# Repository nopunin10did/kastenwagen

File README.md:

# Kastenwagen 1840

Kastenwagen 1840 is a 40% keyboard with a mini-numpad and dedicated arrows.  The main alpha block is 13.75u long, allowing for more dedicated punctuation keys (or non-English letters) to be paired with common Minivan-like mod keys.

Kastenwagen 48 is a similar keyboard that replaces the mini-numpad with a small macro column.

For more information, join the [NoPunIn10Key Discord](https://discord.gg/sku2Y6w).

* Keyboard Maintainer: [Alex Ronke](https://nopunin10did.com/), also known as [NoPunIn10Did](https://github.com/NoPunIn10Did)
* Hardware Supported: Kastenwagen 1840 (2021 June)
* Hardware Availability: Currently by request only

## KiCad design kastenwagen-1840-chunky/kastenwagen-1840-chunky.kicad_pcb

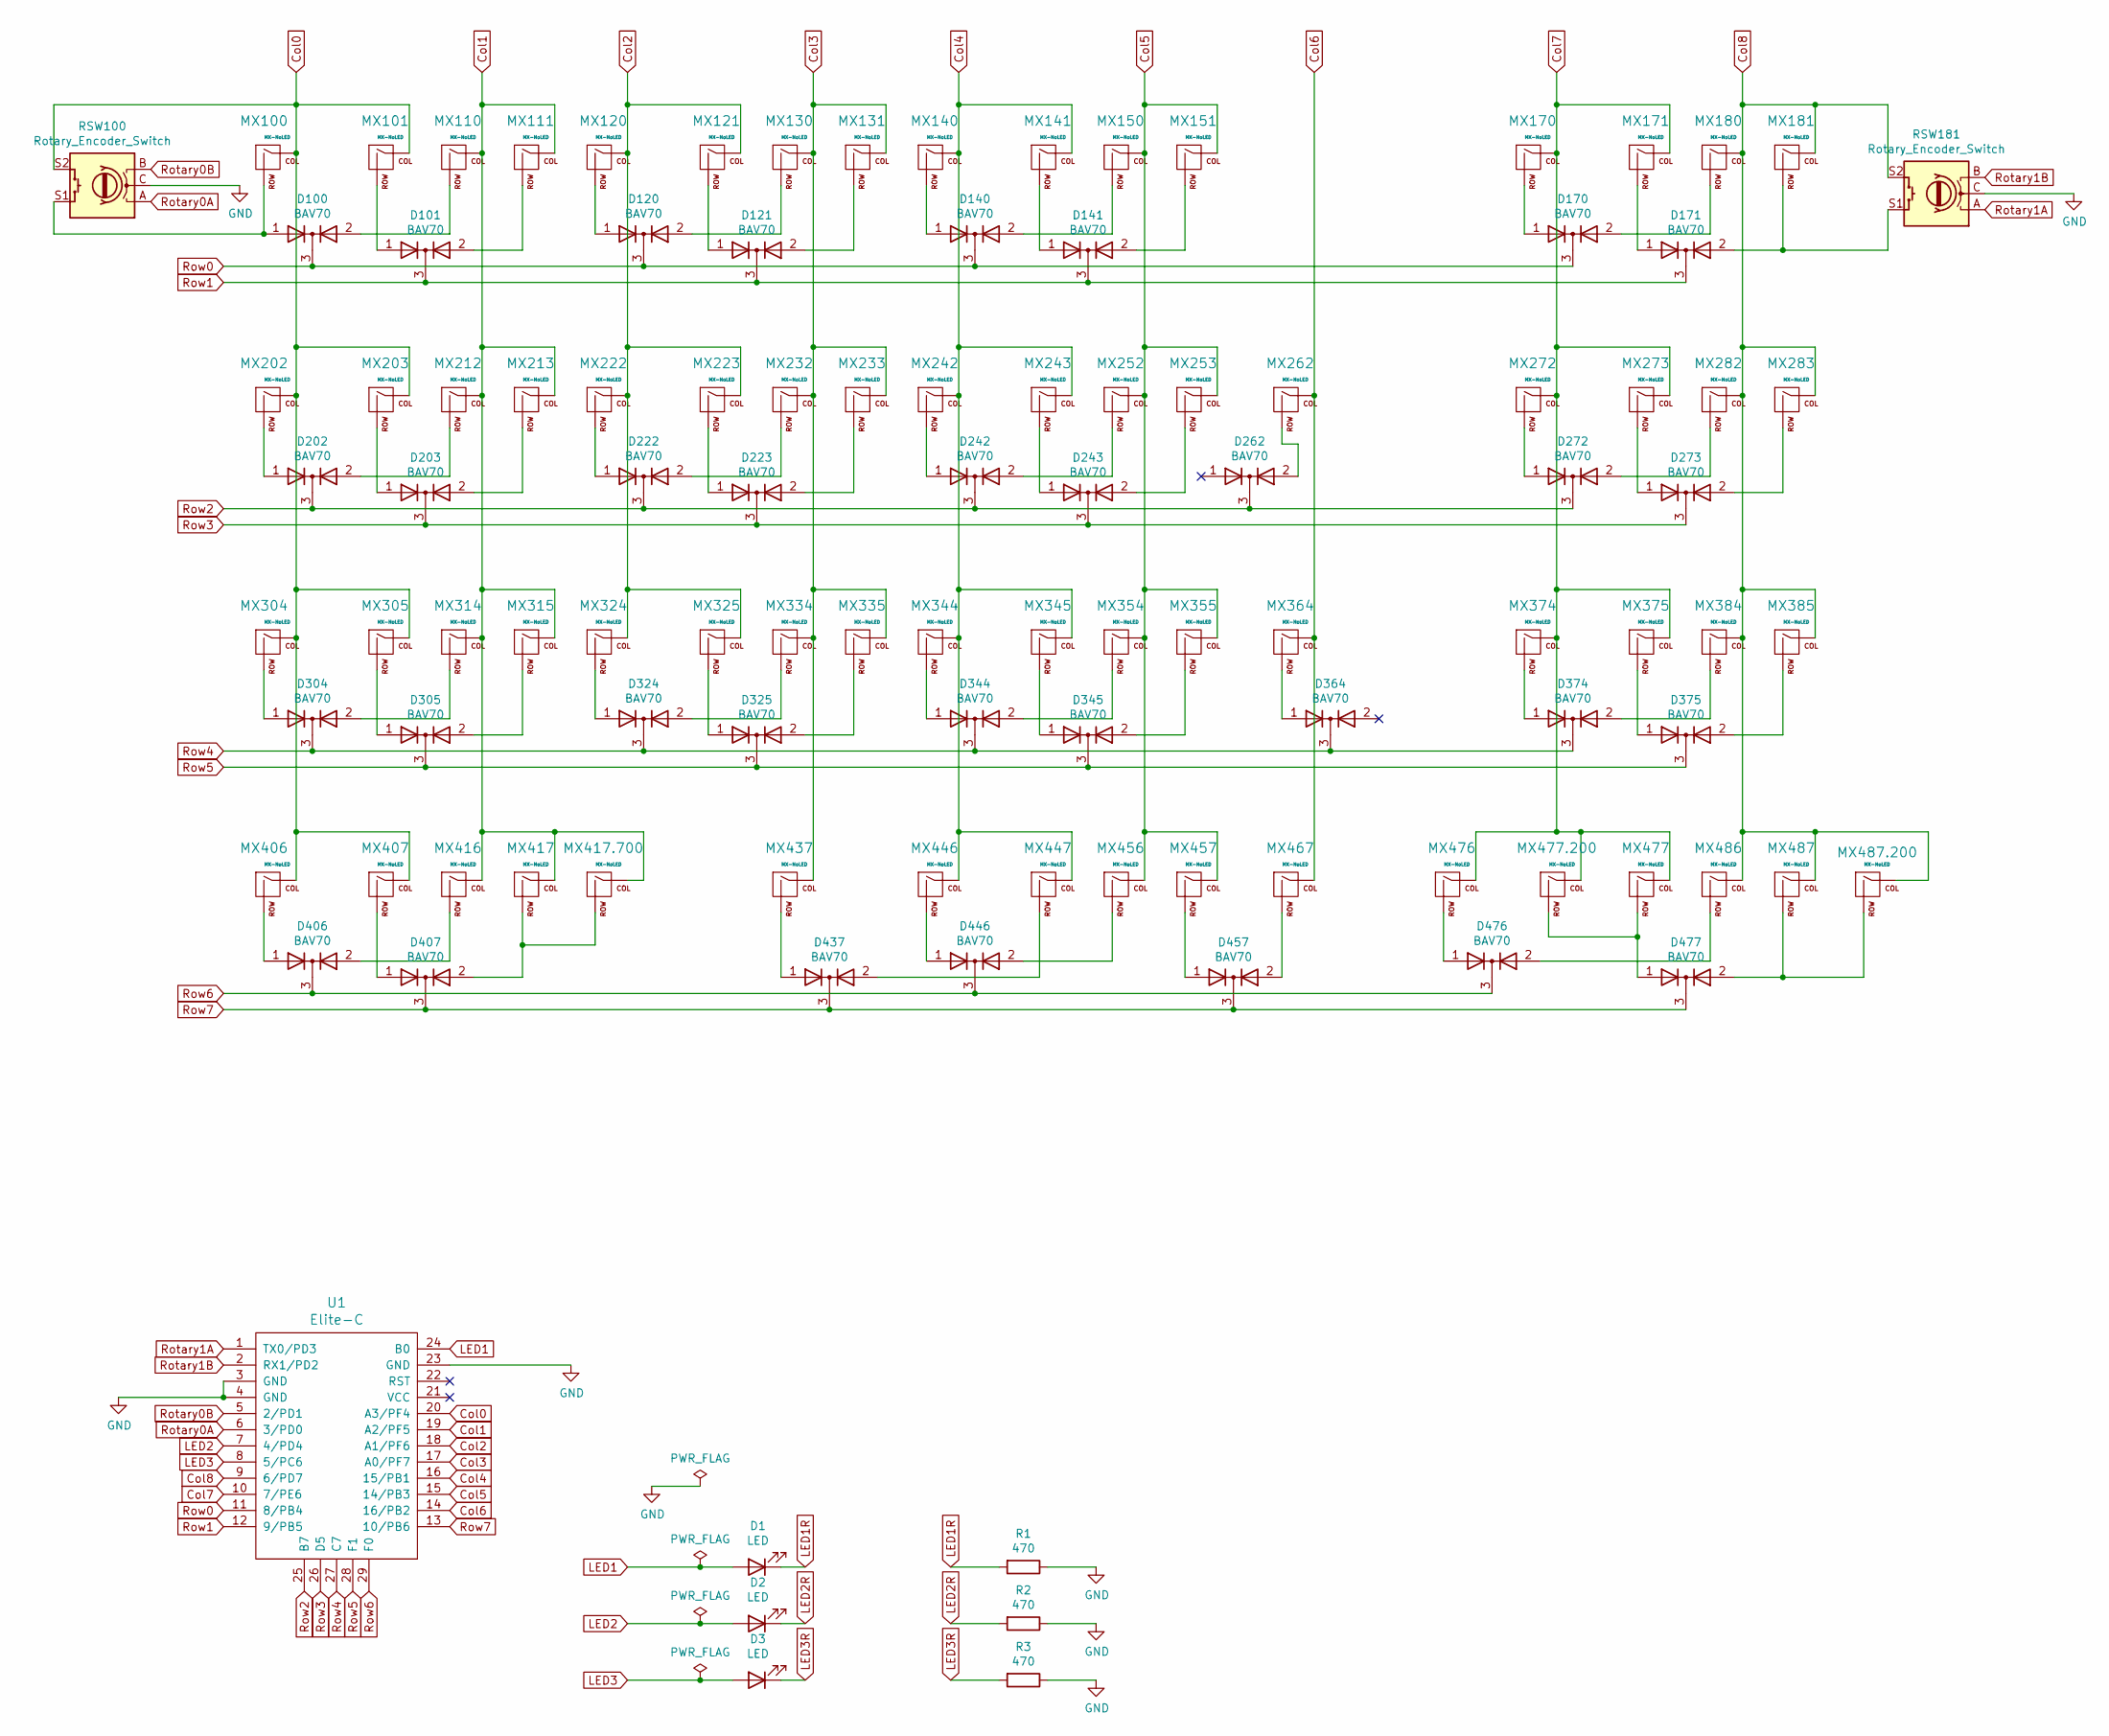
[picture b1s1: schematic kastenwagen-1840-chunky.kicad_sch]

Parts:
D1, D2, D3: LED; LED_1206_3216Metric_Pad1.42x1.75mm_HandSolder
D100, D101, D120, D121, D140, D141, D170, D171, D202, D203, D222, D223, D242, D243, D262, D272, D273, D304, D305, D324, D325, D344, D345, D364, D374, D375, D406, D407, D437, D446, D457, D476, D477: BAV70; SOT-23_Handsoldering
MX100, MX101, MX110, MX111, MX120, MX121, MX130, MX131, MX140, MX141, MX150, MX151, MX170, MX171, MX180, MX181, MX203, MX212, MX213, MX222, MX223, MX232, MX233, MX242, MX243, MX252, MX253, MX272, MX273, MX282, MX283, MX305, MX314, MX315, MX324, MX325, MX334, MX335, MX344, MX345, MX354, MX364, MX374, MX375, MX384, MX385, MX416, MX446, MX457, MX467, MX476, MX477, MX486, MX487: MX-NoLED; MXOnly-1U-NoLED
MX202, MX355, MX406, MX407, MX447, MX456: MX-NoLED; MXOnly-1.25U-NoLED
MX262: MX-NoLED; MXOnly-ISO-ROTATED-NoLED-NoStabs
MX304: MX-NoLED; MXOnly-1.75U-NoLED
MX417: MX-NoLED; MXOnly-2.75U-ReversedStabilizers-NoLED
MX417.700: MX-NoLED; MXOnly-7U-ReversedStabilizers-NoLED
MX437: MX-NoLED; MXOnly-2.25U-ReversedStabilizers-NoLED
MX477.200: MX-NoLED; MXOnly-2U-ReversedStabilizers-NoLED
MX487.200: MX-NoLED; MXOnly-2U-NoLED
R1, R2, R3: 470; R_0805
RSW100, RSW181: Rotary_Encoder_Switch; RotaryEncoder_EC11-no-legs
U1: Elite-C; Elite-C-castellated-29pin-holes

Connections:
Col0: MX100.1 (COL), MX101.1 (COL), MX202.1 (COL), MX203.1 (COL), MX304.1 (COL), MX305.1 (COL), MX406.1 (COL), MX407.1 (COL), RSW100.S2, U1.20 (A3/PF4)
Col1: MX110.1 (COL), MX111.1 (COL), MX212.1 (COL), MX213.1 (COL), MX314.1 (COL), MX315.1 (COL), MX416.1 (COL), MX417.1 (COL), MX417.700.1 (COL), U1.19 (A2/PF5)
Col2: MX120.1 (COL), MX121.1 (COL), MX222.1 (COL), MX223.1 (COL), MX324.1 (COL), MX325.1 (COL), U1.18 (A1/PF6)
Col3: MX130.1 (COL), MX131.1 (COL), MX232.1 (COL), MX233.1 (COL), MX334.1 (COL), MX335.1 (COL), MX437.1 (COL), U1.17 (A0/PF7)
Col4: MX140.1 (COL), MX141.1 (COL), MX242.1 (COL), MX243.1 (COL), MX344.1 (COL), MX345.1 (COL), MX446.1 (COL), MX447.1 (COL), U1.16 (15/PB1)
Col5: MX150.1 (COL), MX151.1 (COL), MX252.1 (COL), MX253.1 (COL), MX354.1 (COL), MX355.1 (COL), MX456.1 (COL), MX457.1 (COL), U1.15 (14/PB3)
Col6: MX262.1 (COL), MX364.1 (COL), MX467.1 (COL), U1.14 (16/PB2)
Col7: MX170.1 (COL), MX171.1 (COL), MX272.1 (COL), MX273.1 (COL), MX374.1 (COL), MX375.1 (COL), MX476.1 (COL), MX477.1 (COL), MX477.200.1 (COL), U1.10 (7/PE6)
Col8: MX180.1 (COL), MX181.1 (COL), MX282.1 (COL), MX283.1 (COL), MX384.1 (COL), MX385.1 (COL), MX486.1 (COL), MX487.1 (COL), MX487.200.1 (COL), RSW181.S2, U1.9 (6/PD7)
GND: R1.1, R2.1, R3.1, RSW100.C, RSW181.C, U1.3 (GND), U1.4 (GND), U1.23 (GND)
LED1: D1.2 (A), U1.24 (B0)
LED1R: D1.1 (K), R1.2
LED2: D2.2 (A), U1.7 (4/PD4)
LED2R: D2.1 (K), R2.2
LED3: D3.2 (A), U1.8 (5/PC6)
LED3R: D3.1 (K), R3.2
unnamed: D100.1 (A), MX100.2 (ROW), RSW100.S1
unnamed: D101.1 (A), MX101.2 (ROW)
unnamed: D100.2 (A), MX110.2 (ROW)
unnamed: D101.2 (A), MX111.2 (ROW)
unnamed: D120.1 (A), MX120.2 (ROW)
unnamed: D121.1 (A), MX121.2 (ROW)
unnamed: D120.2 (A), MX130.2 (ROW)
unnamed: D121.2 (A), MX131.2 (ROW)
unnamed: D140.1 (A), MX140.2 (ROW)
unnamed: D141.1 (A), MX141.2 (ROW)
unnamed: D140.2 (A), MX150.2 (ROW)
unnamed: D141.2 (A), MX151.2 (ROW)
unnamed: D170.1 (A), MX170.2 (ROW)
unnamed: D171.1 (A), MX171.2 (ROW)
unnamed: D170.2 (A), MX180.2 (ROW)
unnamed: D171.2 (A), MX181.2 (ROW), RSW181.S1
unnamed: D202.1 (A), MX202.2 (ROW)
unnamed: D203.1 (A), MX203.2 (ROW)
unnamed: D202.2 (A), MX212.2 (ROW)
unnamed: D203.2 (A), MX213.2 (ROW)
unnamed: D222.1 (A), MX222.2 (ROW)
unnamed: D223.1 (A), MX223.2 (ROW)
unnamed: D222.2 (A), MX232.2 (ROW)
unnamed: D223.2 (A), MX233.2 (ROW)
unnamed: D242.1 (A), MX242.2 (ROW)
unnamed: D243.1 (A), MX243.2 (ROW)
unnamed: D242.2 (A), MX252.2 (ROW)
unnamed: D243.2 (A), MX253.2 (ROW)
unnamed: D262.2 (A), MX262.2 (ROW)
unnamed: D272.1 (A), MX272.2 (ROW)
unnamed: D273.1 (A), MX273.2 (ROW)
unnamed: D272.2 (A), MX282.2 (ROW)
unnamed: D273.2 (A), MX283.2 (ROW)
unnamed: D304.1 (A), MX304.2 (ROW)
unnamed: D305.1 (A), MX305.2 (ROW)
unnamed: D304.2 (A), MX314.2 (ROW)
unnamed: D305.2 (A), MX315.2 (ROW)
unnamed: D324.1 (A), MX324.2 (ROW)
unnamed: D325.1 (A), MX325.2 (ROW)
unnamed: D324.2 (A), MX334.2 (ROW)
unnamed: D325.2 (A), MX335.2 (ROW)
unnamed: D344.1 (A), MX344.2 (ROW)
unnamed: D345.1 (A), MX345.2 (ROW)
unnamed: D344.2 (A), MX354.2 (ROW)
unnamed: D345.2 (A), MX355.2 (ROW)
unnamed: D364.1 (A), MX364.2 (ROW)
unnamed: D374.1 (A), MX374.2 (ROW)
unnamed: D375.1 (A), MX375.2 (ROW)
unnamed: D374.2 (A), MX384.2 (ROW)
unnamed: D375.2 (A), MX385.2 (ROW)
unnamed: D406.1 (A), MX406.2 (ROW)
unnamed: D407.1 (A), MX407.2 (ROW)
unnamed: D406.2 (A), MX416.2 (ROW)
unnamed: D407.2 (A), MX417.2 (ROW), MX417.700.2 (ROW)
unnamed: D437.1 (A), MX437.2 (ROW)
unnamed: D446.1 (A), MX446.2 (ROW)
unnamed: D437.2 (A), MX447.2 (ROW)
unnamed: D446.2 (A), MX456.2 (ROW)
unnamed: D457.1 (A), MX457.2 (ROW)
unnamed: D457.2 (A), MX467.2 (ROW)
unnamed: D476.1 (A), MX476.2 (ROW)
unnamed: D477.1 (A), MX477.2 (ROW), MX477.200.2 (ROW)
unnamed: D476.2 (A), MX486.2 (ROW)
unnamed: D477.2 (A), MX487.2 (ROW), MX487.200.2 (ROW)
Rotary0A: RSW100.A, U1.6 (3/PD0)
Rotary0B: RSW100.B, U1.5 (2/PD1)
Rotary1A: RSW181.A, U1.1 (TX0/PD3)
Rotary1B: RSW181.B, U1.2 (RX1/PD2)
Row0: D100.3 (K), D120.3 (K), D140.3 (K), D170.3 (K), U1.11 (8/PB4)
Row1: D101.3 (K), D121.3 (K), D141.3 (K), D171.3 (K), U1.12 (9/PB5)
Row2: D202.3 (K), D222.3 (K), D242.3 (K), D262.3 (K), D272.3 (K), U1.25 (B7)
Row3: D203.3 (K), D223.3 (K), D243.3 (K), D273.3 (K), U1.26 (D5)
Row4: D304.3 (K), D324.3 (K), D344.3 (K), D364.3 (K), D374.3 (K), U1.27 (C7)
Row5: D305.3 (K), D325.3 (K), D345.3 (K), D375.3 (K), U1.28 (F1)
Row6: D406.3 (K), D446.3 (K), D476.3 (K), U1.29 (F0)
Row7: D407.3 (K), D437.3 (K), D457.3 (K), D477.3 (K), U1.13 (10/PB6)

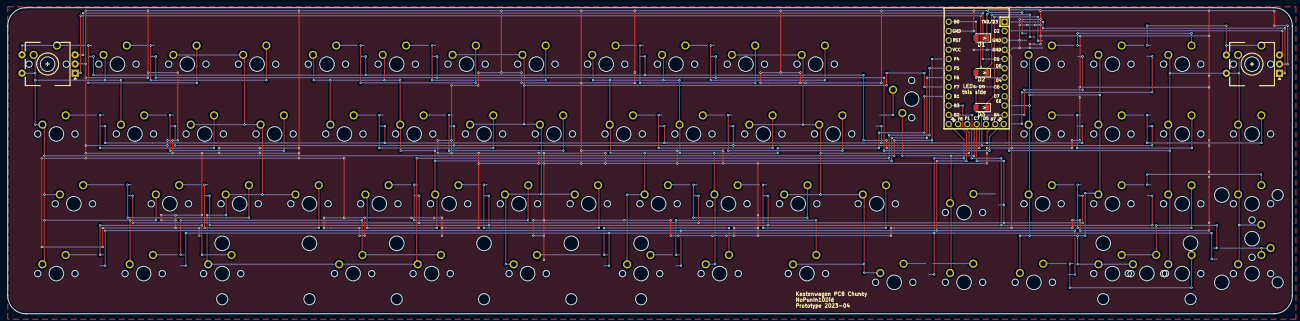
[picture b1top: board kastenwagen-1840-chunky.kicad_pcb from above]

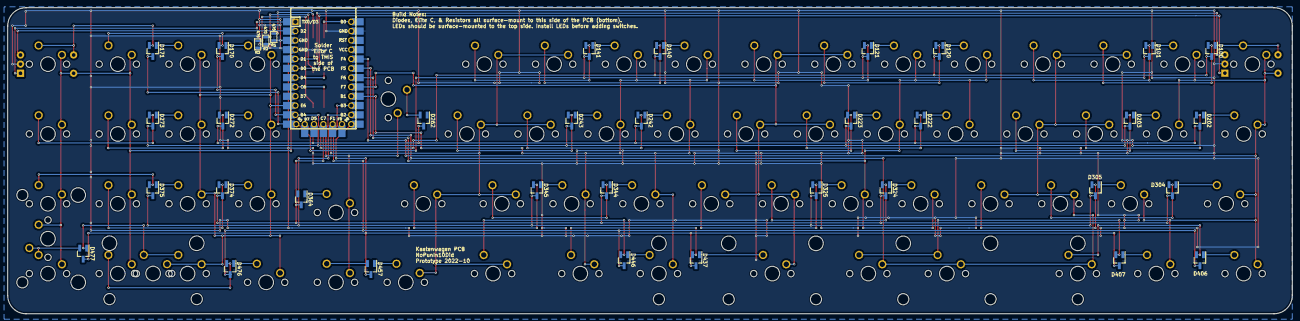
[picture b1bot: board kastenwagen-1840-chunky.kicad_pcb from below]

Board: 2 copper layers, 350.5 x 83.5 mm, 109 parts (37 on the bottom side), 92 nets.

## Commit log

2021-03-04 schema WIP
2021-03-04 Complete Schema
2021-03-04 first draft routing
2021-03-05 Plate WIP
2021-03-09 Reverse the stabilizers
2021-03-23 drawing edge cuts
2021-03-23 post license
2021-03-23 Ground planes
2021-03-23 Plate edits and LED positioning
2021-03-23 bottom plate and tweaks
2021-03-24 tweak
2021-03-29 Tweaks
2021-03-29 Make backup of PCB using elite C
2021-03-29 On-board MCU to universal daughterboard
2021-04-06 Add PCB and Schema for 48
2021-06-08 Kastenwagen 1840 plate gerbers
2021-06-08 Kastenwagen 1840 PCB Gerbers
2021-06-08 Further gerber updates
2021-06-08 Kastenwagen 48 gerbers
2021-06-08 more gerber amendments
2021-06-15 Updated plate bezels and gerbers
2021-06-18 Footprint & Gerber updates
2021-07-21 Fixup
2022-07-14 gerber zips
2022-09-22 Reorganize folders
2022-09-22 Rename primary directory
2022-09-22 redoing traces
2022-09-22 More tracing updates
2022-10-26 Update Kastenwagen open source license
2023-04-10 Initial fiddling, adding the chunky ISO
2023-04-10 Fix the ISO footprint used and retrace where needed
2023-04-12 Export gerbers
2023-04-12 Add amended plate, gerbers, and SVG
